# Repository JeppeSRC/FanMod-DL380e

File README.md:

# FanMod-DL380e
DL380e G8 fan mod

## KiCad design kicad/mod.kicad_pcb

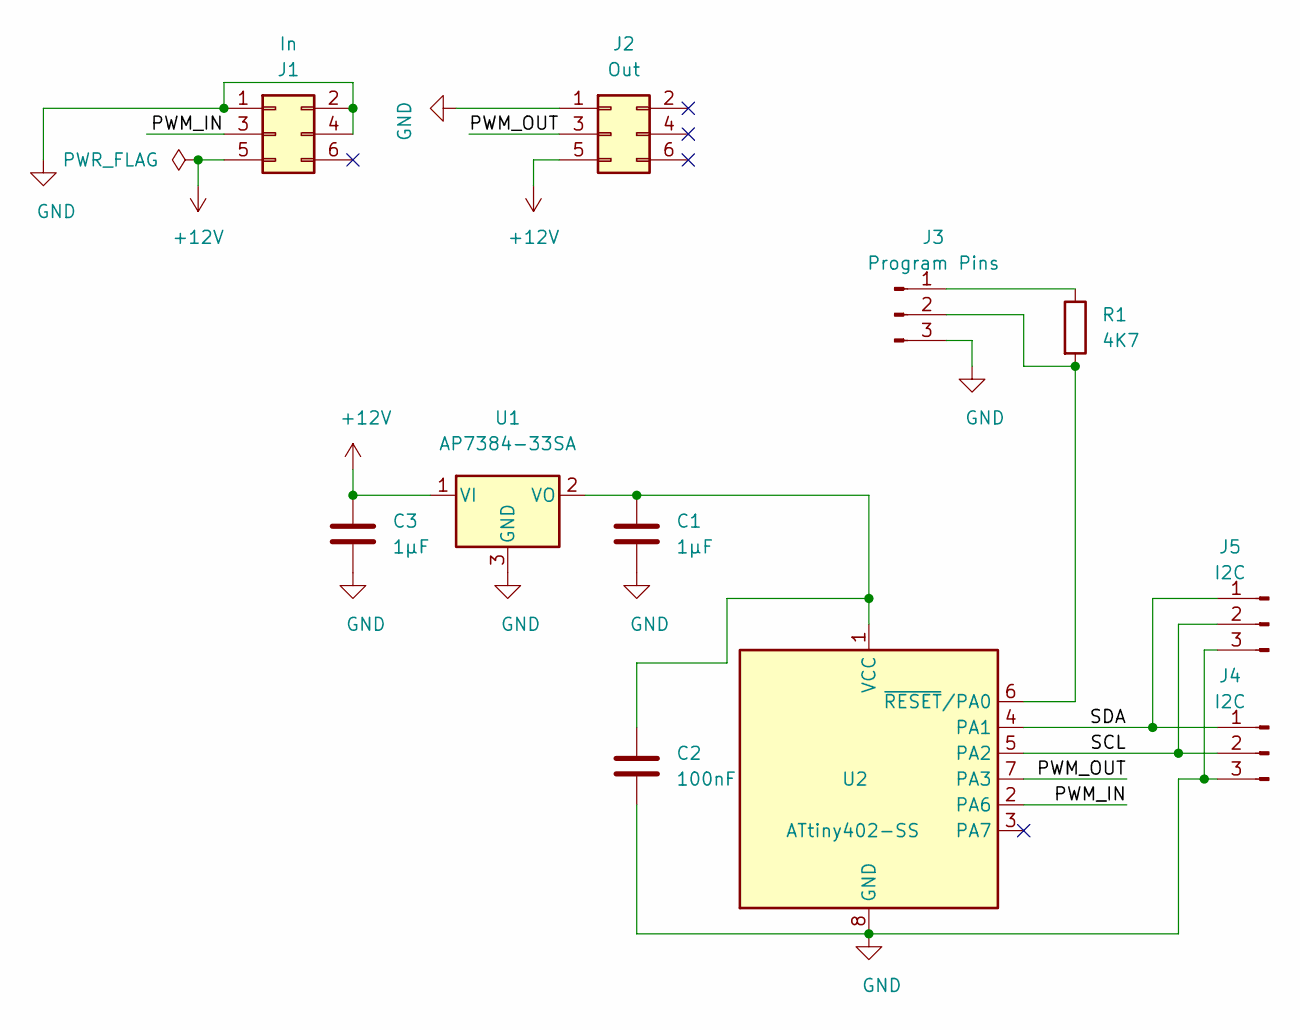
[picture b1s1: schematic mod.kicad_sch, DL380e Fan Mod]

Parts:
C1, C3: 1µF; C_0805_2012Metric
C2: 100nF; C_0805_2012Metric
J1: In; PinHeader_2x03_P2.00mm_Vertical
J2: Out; PinHeader_2x03_P2.00mm_Vertical
J3: Program Pins; PinHeader_1x03_P2.54mm_Vertical
J4, J5: I2C; PinHeader_1x03_P2.54mm_Vertical
R1: 4K7; C_0805_2012Metric
U1: AP7384-33SA; SOT-23
U2: ATtiny402-SS; SOIC-8_3.9x4.9mm_P1.27mm

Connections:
+12V: C3.1, J1.5, J2.5, U1.1 (VI)
/PWM_IN: J1.3, U2.2 (PA6)
/PWM_OUT: J2.3, U2.7 (PA3)
/SCL: J4.2, J5.2, U2.5 (PA2)
/SDA: J4.1, J5.1, U2.4 (PA1)
GND: C1.2, C2.1, C3.2, J1.1, J1.2, J1.4, J2.1, J3.3, J4.3, J5.3, U1.3 (GND), U2.8 (GND)
unnamed: C1.1, C2.2, U1.2 (VO), U2.1 (VCC)
unnamed: J3.1, R1.1
unnamed: J3.2, R1.2, U2.6 (~RESET~/PA0)

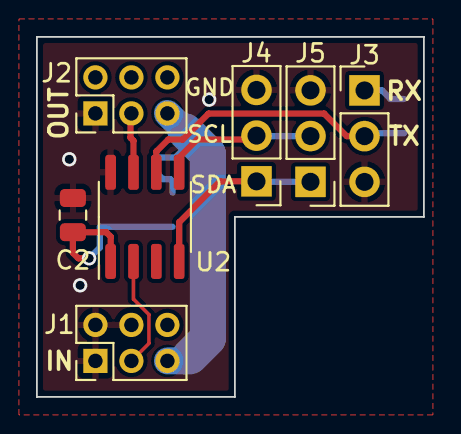
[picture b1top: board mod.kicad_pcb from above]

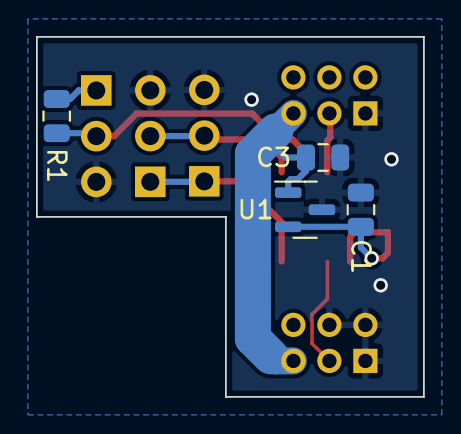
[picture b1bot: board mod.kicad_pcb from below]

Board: 2 copper layers, 21.5 x 20.0 mm, 11 parts (4 on the bottom side), 9 nets.

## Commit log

2021-02-23 Create LICENSE
2021-02-27 Added some datasheets
2021-02-27 Kicad project and kinda finished schematicx
2021-02-27 Added another datasheet
2021-02-27 Started layout
2021-03-02 Meh 2
2021-03-02 Yeeet
2021-03-02 Kinda complete
2021-03-09 Fixed project to work on other PCs
2021-03-10 Done with pcb
2021-03-11 Deleted file that shouldn't exist
2021-03-11 Sure
2021-03-11 Removed folder
2021-03-18 Added vs project
2021-03-18 Startup code
2021-03-18 Updated gitignore
2021-03-19 Moved startup to different folder and changed jmp main to call main
2021-03-19 Added typedefs
2021-03-19 Added CPUINT register
2021-03-19 Project stuff
2021-03-20 Added sys read and write
2021-03-20 Update cpuint
2021-03-20 Added clkctrl
2021-03-20 Enabled lto
2021-03-20 Replaced tabs with spaces
2021-03-20 Whoopsie forgottie thesei
2021-03-20 Prefixes
2021-03-20 Added prefix to bitflags
2021-03-20 Added readw and writew
2021-03-20 Added tca0 registers
2021-03-21 Added -fno-builtin
2021-03-21 Added some math stuff
2021-03-21 Changed register writing and reading
2021-03-21 Moved sys include to c file
2021-03-21 Added TCB0
2021-03-21 Added evsys
2021-03-21 Fixed typo
2021-03-21 Added twi
2021-03-21 Changed name of log2 to stop the compiler from bitching
2021-03-21 twi_init
2021-03-21 Added TWIS irq
2021-03-22 Fix to prevent the compiler from doing stupid
2021-03-22 Fixed typo but made another typo
2021-03-22 Eh 3
2021-03-22 Removed annoying 0 from counter names
2021-03-22 tca setup for 25KHz PWM
2021-03-22 Removed tca prescaler
2021-03-23 Added PORT register
2021-03-23 Set PA3 to output
2021-03-23 Yeeted a 0
2021-03-23 Fixed Fixed typo
2021-03-23 Frequency measurements implemented
2021-03-25 Server uses inverted PWM
2021-03-25 Set MCU frequency to 10MHz
2021-05-12 Testing
2021-05-12 Added write to CCP register for protected registers
2021-05-12 Converting elf to hex
2021-05-12 SAtill testing
2021-05-13 Port pin control
2021-05-15 Added more cpu register stuff
2021-05-15 Hopefully working
2021-05-15 Stupid
2021-05-15 Test
2023-11-04 Added include dir to solution because it wasen't there for some reason
